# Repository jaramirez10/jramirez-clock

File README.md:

# jramirez-clock
 This repository contains all files pertaining to my PCB clock design and development as part of the Google Hardware Product Sprint.

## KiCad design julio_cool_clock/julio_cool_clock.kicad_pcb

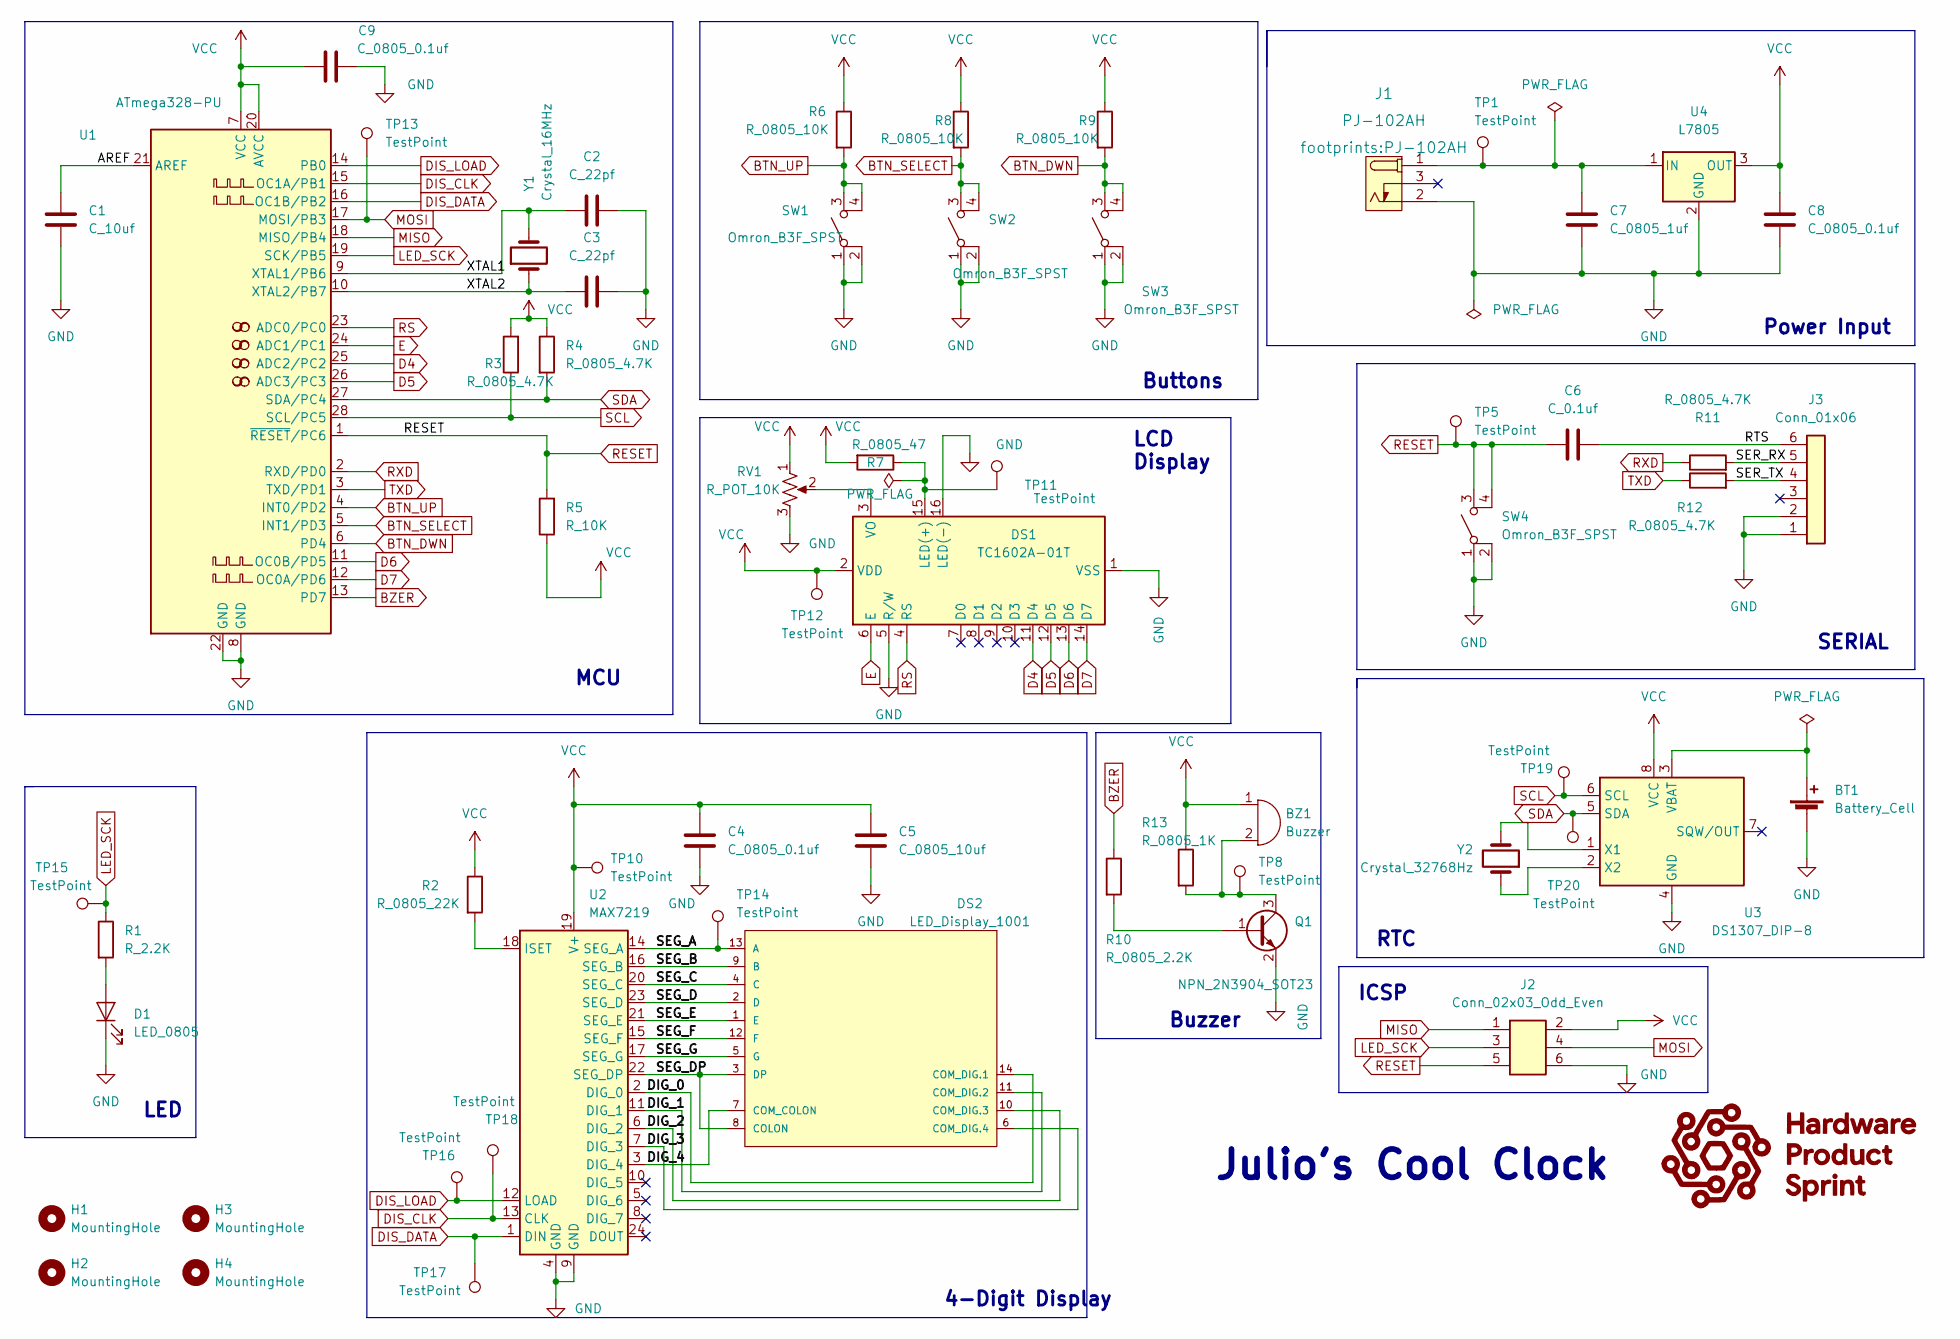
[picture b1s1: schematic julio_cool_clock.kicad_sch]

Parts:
BT1: Battery_Cell; BatteryHolder_Keystone_106_1x20mm; MPN BS-7; Digikey PN BS-7-ND
BZ1: Buzzer; Buzzer_TDK_PS1240P02BT_D12.2mm_H6.5mm; MPN PS1420P02CT; Digikey PN 445-2526-1-ND
C1: C_10uf; C_0805_2012Metric; Voltage N/A; Tolerance N/A; MPN GRM21BR61E106KA73L; Digikey PN 490-5523-1-ND
C2, C3: C_22pf; C_0805_2012Metric; Voltage N/A; Tolerance N/A; MPN CC0805JRNPO9BN220; Digikey PN 311-1103-1-ND
C4, C8, C9: C_0805_0.1uf; C_0805_2012Metric; Voltage N/A; Tolerance N/A; MPN 08055C104KAT2A; Digikey PN 478-1395-1-ND
C5: C_0805_10uf; C_0805_2012Metric; Voltage N/A; Tolerance N/A; MPN GRM21BR61E106KA73L; Digikey PN 490-5523-1-ND
C6: C_0.1uf; C_0805_2012Metric; Voltage N/A; Tolerance N/A; MPN 08055C104KAT2A; Digikey PN 478-1395-1-ND
C7: C_0805_1uf; C_0805_2012Metric; Voltage N/A; Tolerance N/A; MPN CC0805KKX7R8BB105; Digikey PN 311-1456-1-ND
D1: LED_0805; LED_0805_2012Metric; MPN 150080RS75000; Digikey PN 732-4984-1-ND
DS1: TC1602A-01T; MPN 1447; Digikey PN 1528-2212-ND
DS2: LED_Display_1001; Adafruit-1001-0-0-MFG; forward voltage 3.2V; reverse voltage 5V; mouser part number 485-1001; digikey description WHITE 7-SEGMENT CLOCK DISPLAY
H1, H2, H3, H4: MountingHole; MountingHole_3.2mm_M3
J1: PJ-102AH; MPN PJ-102AH; Digikey PN CP-102AH-ND
J2: Conn_02x03_Odd_Even; PinHeader_2x03_P2.54mm_Vertical; MPN PRPC003DAAN-RC; Digikey PN S2011EC-03-ND
J3: Conn_01x06; PinHeader_1x06_P2.54mm_Vertical; MPN 61300611121; Digikey PN 732-5319-ND
Q1: NPN_2N3904_SOT23; SOT-23; MPN CMPT3904E TR PBFREE; Digikey PN 1514-CMPT3904ETRPBFREECT-ND
R1: R_2.2K; R_0805_2012Metric; Tolerance N/A; MPN N/A; Digikey PN 311-2.20KCRCT-ND
R2: R_0805_22K; R_0805_2012Metric; Tolerance N/A; MPN RC0805FR-0722KL; Digikey PN 311-22.0KCRCT-ND
R3, R4, R11, R12: R_0805_4.7K; R_0805_2012Metric; Tolerance N/A; MPN RC0805FR-074K7L; Digikey PN 311-4.70KCRCT-ND
R5: R_10K; R_0805_2012Metric; Tolerance N/A; MPN RC0805FR-0710KL; Digikey PN 311-10.0KCRCT-ND
R6, R8, R9: R_0805_10K; R_0805_2012Metric; Tolerance N/A; MPN RC0805FR-0710KL; Digikey PN 311-10.0KCRCT-ND
R7: R_0805_47; R_0805_2012Metric; Tolerance N/A; Mouser PN N/A; Digikey PN RC0805FR-0747RL
R10: R_0805_2.2K; R_0805_2012Metric; Tolerance N/A; MPN N/A; Digikey PN 311-2.20KCRCT-ND
R13: R_0805_1K; R_0805_2012Metric; Tolerance N/A; Mouser PN N/A; Digikey PN RC0805FR-0710KL
RV1: R_POT_10K; Potentiometer_Bourns_3386P_Vertical; MPN 3386P-1-103TLF; Digikey PN 3386P-103TLF-ND
SW1, SW2, SW3, SW4: Omron_B3F_SPST; SW_SPST_Omron_B3FS-100xP; MPN B3FS-1000P; Digikey PN SW423CT-ND
TP1, TP5, TP8, TP10, TP11, TP12, TP13, TP14, TP15, TP16, TP17, TP18, TP19, TP20: TestPoint; TestPoint_THTPad_D2.0mm_Drill1.0mm
U1: ATmega328-PU; DIP-28_W7.62mm; MPN ED281DT; Digikey PN ED3050-5-ND
U2: MAX7219; DIP-24_W7.62mm; MPN ED241DT; Digikey PN ED3049-5-ND
U3: DS1307_DIP-8; DIP-8_W7.62mm; MPN A 08-LC-TT; Digikey PN AE9986-ND
U4: L7805; TO-252-2; MPN L7805CDT-TR; Digikey PN 497-7255-1-ND
Y1: Crystal_16MHz; Crystal_SMD_HC49-SD; MPN ECS-160-20-5PXDN-TR; Digikey PN XC1299CT-ND
Y2: Crystal_32768Hz; Crystal_SMD_2Pin_3.2x1.5mm; MPN Q 0,032768-JTX310-12,5-20-T1-HMR-50K-LF; Digikey PN 1908-1314-1-ND

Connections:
/AREF: C1.1, U1.21 (AREF)
/DIG_0: DS2.14 (COM_DIG.1), U2.2 (DIG_0)
/DIG_1: DS2.11 (COM_DIG.2), U2.11 (DIG_1)
/DIG_2: DS2.10 (COM_DIG.3), U2.6 (DIG_2)
/DIG_3: DS2.6 (COM_DIG.4), U2.7 (DIG_3)
/DIG_4: DS2.7 (COM_COLON), U2.3 (DIG_4)
/RTS: C6.2, J3.6
/SEG_A: DS2.13 (A), TP14.1, U2.14 (SEG_A)
/SEG_B: DS2.9 (B), U2.16 (SEG_B)
/SEG_C: DS2.4 (C), U2.20 (SEG_C)
/SEG_D: DS2.2 (D), U2.23 (SEG_D)
/SEG_DP: DS2.3 (DP), DS2.8 (COLON), U2.22 (SEG_DP)
/SEG_E: DS2.1 (E), U2.21 (SEG_E)
/SEG_F: DS2.12 (F), U2.15 (SEG_F)
/SEG_G: DS2.5 (G), U2.17 (SEG_G)
/SER_RX: J3.5, R11.2
/SER_TX: J3.4, R12.2
/XTAL1: C2.1, U1.9 (XTAL1/PB6), Y1.2
/XTAL2: C3.2, U1.10 (XTAL2/PB7), Y1.1
BTN_DWN: R9.2, SW3.3 (B), SW3.4 (B), U1.6 (PD4)
BTN_SELECT: R8.2, SW2.3 (B), SW2.4 (B), U1.5 (INT1/PD3)
BTN_UP: R6.2, SW1.3 (B), SW1.4 (B), U1.4 (INT0/PD2)
BZER: R10.1, U1.13 (PD7)
D4: DS1.11 (D4), U1.25 (ADC2/PC2)
D5: DS1.12 (D5), U1.26 (ADC3/PC3)
D6: DS1.13 (D6), U1.11 (OC0B/PD5)
D7: DS1.14 (D7), U1.12 (OC0A/PD6)
DIS_CLK: TP18.1, U1.15 (OC1A/PB1), U2.13 (CLK)
DIS_DATA: TP17.1, U1.16 (OC1B/PB2), U2.1 (DIN)
DIS_LOAD: TP16.1, U1.14 (PB0), U2.12 (LOAD)
E: DS1.6 (E), U1.24 (ADC1/PC1)
GND: BT1.2 (-), C1.2, C2.2, C3.1, C4.2, C5.2, C7.2, C8.2, C9.2, D1.1 (K), DS1.1 (VSS), DS1.5 (R/W), DS1.16 (LED(-)), J1.2 (OUT), J2.6, J3.1, J3.2, Q1.2 (E), RV1.3, SW1.1 (A), SW1.2 (A), SW2.1 (A), SW2.2 (A), SW3.1 (A), SW3.2 (A), SW4.1 (A), SW4.2 (A), U1.8 (GND), U1.22 (GND), U2.4 (GND), U2.9 (GND), U3.4 (GND), U4.2 (GND)
LED_SCK: J2.3, R1.1, TP15.1, U1.19 (SCK/PB5)
MISO: J2.1, U1.18 (MISO/PB4)
MOSI: J2.4, TP13.1, U1.17 (MOSI/PB3)
unnamed: BT1.1 (+), U3.3 (VBAT)
unnamed: BZ1.2 (+), Q1.3 (C), R13.2, TP8.1
unnamed: C7.1, J1.1 (POLE), TP1.1, U4.1 (IN)
unnamed: D1.2 (A), R1.2
unnamed: DS1.3 (VO), RV1.2
unnamed: DS1.15 (LED(+)), R7.1, TP11.1
unnamed: Q1.1 (B), R10.2
unnamed: R2.2, U2.18 (ISET)
unnamed: U3.1 (X1), Y2.2
unnamed: U3.2 (X2), Y2.1
RESET: C6.1, J2.5, R5.2, SW4.3 (B), SW4.4 (B), TP5.1, U1.1 (~RESET/PC6)
RS: DS1.4 (RS), U1.23 (ADC0/PC0)
RXD: R11.1, U1.2 (RXD/PD0)
SCL: R3.1, TP19.1, U1.28 (SCL/PC5), U3.6 (SCL)
SDA: R4.2, TP20.1, U1.27 (SDA/PC4), U3.5 (SDA)
TXD: R12.1, U1.3 (TXD/PD1)
VCC: BZ1.1 (-), C4.1, C5.1, C8.1, C9.1, DS1.2 (VDD), J2.2, R2.1, R3.2, R4.1, R5.1, R6.1, R7.2, R8.1, R9.1, R13.1, RV1.1, TP10.1, TP12.1, U1.7 (VCC), U1.20 (AVCC), U2.19 (V+), U3.8 (VCC), U4.3 (OUT)

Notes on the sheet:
Buttons
MCU
Power Input
LCD Display
LED
Julio's Cool Clock
RTC
4-Digit Display
SERIAL
Buzzer
ICSP

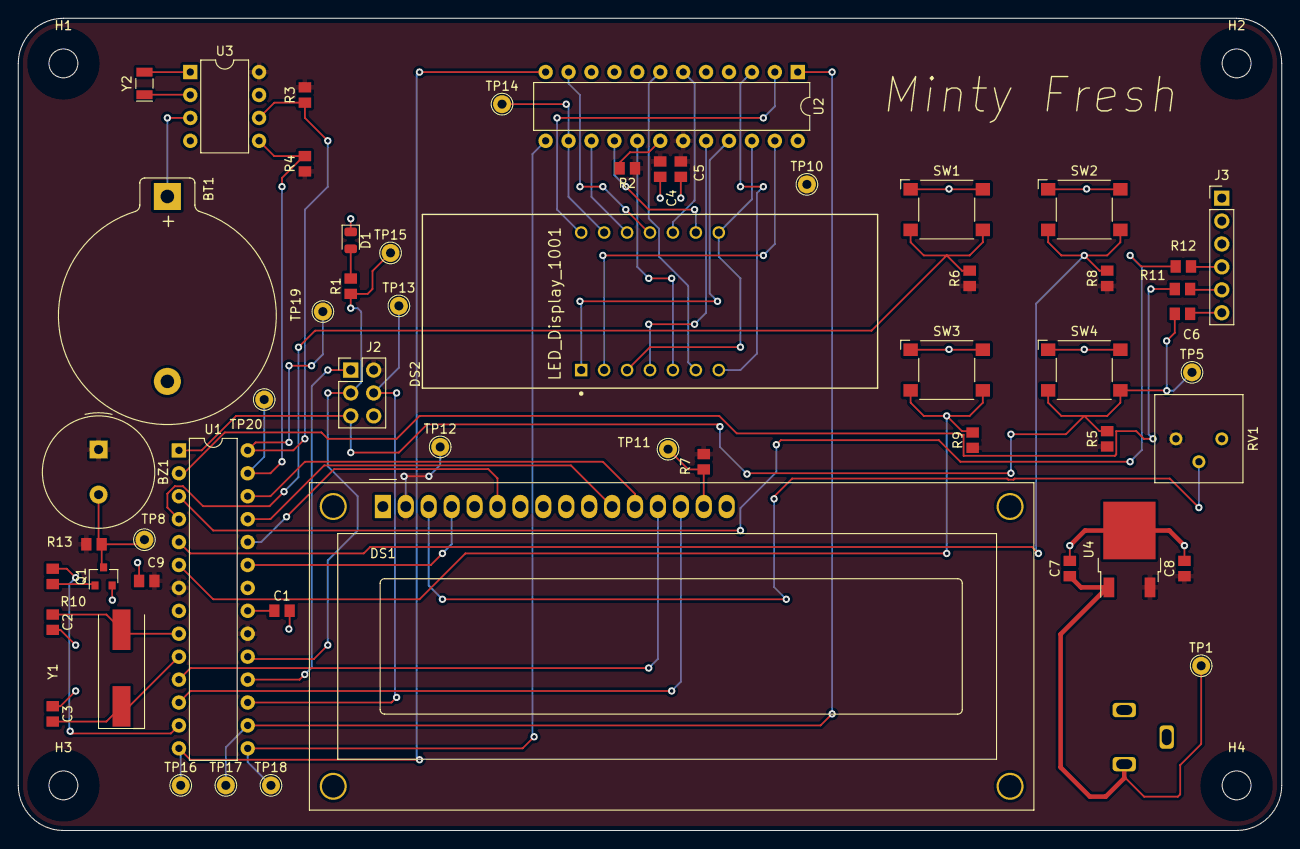
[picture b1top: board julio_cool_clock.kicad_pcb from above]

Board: 2 copper layers, 140.0 x 90.0 mm, 60 parts (1 on the bottom side), 52 nets.

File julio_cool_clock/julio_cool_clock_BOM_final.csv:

"Id";"Designator";"Package";"Quantity";"Designation";"Supplier and ref";
1;"R12,R11,R4,R3";"R_0805_2012Metric";4;"R_0805_4.7K";;;
2;"H4,H2,H3,H1";"MountingHole_3.2mm_M3";4;"MountingHole";;;
3;"TP11,TP15,TP12,TP1,TP17,TP19,TP16,TP13,TP5,TP10,TP18,TP8,TP14,TP20";"TestPoint_THTPad_D2.0mm_Drill1.0mm";14;"TestPoint";;;
4;"C5";"C_0805_2012Metric";1;"C_0805_10uf";;;
5;"C8,C4,C9";"C_0805_2012Metric";3;"C_0805_0.1uf";;;
6;"DS1";"TC1602A-01T";1;"TC1602A-01T";;;
7;"R7";"R_0805_2012Metric";1;"R_0805_47";;;
8;"BZ1";"Buzzer_TDK_PS1240P02BT_D12.2mm_H6.5mm";1;"Buzzer";;;
9;"R13";"R_0805_2012Metric";1;"R_0805_1K";;;
10;"C6";"C_0805_2012Metric";1;"C_0.1uf";;;
11;"R10";"R_0805_2012Metric";1;"R_0805_2.2K";;;
12;"SW2,SW4,SW3,SW1";"SW_SPST_Omron_B3FS-100xP";4;"Omron_B3F_SPST";;;
13;"Y1";"Crystal_SMD_HC49-SD";1;"Crystal_16MHz";;;
14;"R2";"R_0805_2012Metric";1;"R_0805_22K";;;
15;"U1";"DIP-28_W7.62mm";1;"ATmega328-PU";;;
16;"C3,C2";"C_0805_2012Metric";2;"C_22pf";;;
17;"RV1";"Potentiometer_Bourns_3386P_Vertical";1;"R_POT_10K";;;
18;"C1";"C_0805_2012Metric";1;"C_10uf";;;
19;"J2";"PinHeader_2x03_P2.54mm_Vertical";1;"Conn_02x03_Odd_Even";;;
20;"Q1";"SOT-23";1;"NPN_2N3904_SOT23";;;
21;"R6,R9,R8";"R_0805_2012Metric";3;"R_0805_10K";;;
22;"J3";"PinHeader_1x06_P2.54mm_Vertical";1;"Conn_01x06";;;
23;"U2";"DIP-24_W7.62mm";1;"MAX7219";;;
24;"Y2";"Crystal_SMD_2Pin_3.2x1.5mm";1;"Crystal_32768Hz";;;
25;"R1";"R_0805_2012Metric";1;"R_2.2K";;;
26;"D1";"LED_0805_2012Metric";1;"LED_0805";;;
27;"U3";"DIP-8_W7.62mm";1;"DS1307_DIP-8";;;
28;"DS2";"Adafruit-1001-0-0-MFG";1;"LED_Display_1001";;;
29;"U4";"TO-252-2";1;"L7805";;;
30;"BT1";"BatteryHolder_Keystone_106_1x20mm";1;"Battery_Cell";;;
31;"C7";"C_0805_2012Metric";1;"C_0805_1uf";;;
32;"R5";"R_0805_2012Metric";1;"R_10K";;;
33;"J1";"PJ-102AH";1;"VAL**";;;

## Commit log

2022-06-02 Design Commit 1
2022-06-10 Clock Design 1
2022-06-11 New Blinking Speed Commit
    Here is the firmware with the new LED blinking speed as part of the Week 1 deliverables.
2022-06-12 Design Commit 1.1
    Adjusted the starting schematic with 10uF capacitors in place of the polar capacitors in the lecture slide.
2022-06-17 Design Commit 2
    In this commit, I adjusted the MCU schematic section and added the power input portion.
2022-06-20 Design Commit 2.1
    Converted the RESET, RXD, and TXD labels from global inputs to outputs
2022-06-27 Design Commit 3
    Cleaned up the existing components and added inputs + outputs to the schematic as well.
2022-07-04 Design Commit 4
    I refined the schematic and added the RTC, buttons, and the LCD display for my clock.
2022-07-04 Design Commit 4.1
    Fixed some wiring that was undone.
2022-07-06 Design Commit 4.2
    Arranged components from schematic onto PCB.
2022-07-11 Design Commit 5
    Pushed Netlist to PCB and made initial placement of all components, including UI components.
2022-07-17 Design Commit 6
    Added prelim DFT features, completed PCB routing, and shipped first Gerber out.
2022-07-21 Final Gerber
    Git commit for final Gerber Out. I forgot to upload the Google Form for the initial Gerber but everything from the first one is in the previous Git commit.
2022-07-21 Gerber Out Revisions 1
2022-07-21 Final Gerber Out (with revisions)
2022-08-01 MTP Firmware Commit
    First commit for MTP. Program includes code for all components used in my clock.
2022-08-08 MTP Firmware Commit 2
    Made revisions to programs to test the buzzer and buttons after rewiring my dev board. This commit includes all individual MTPs for each I/O as well as one compiled MTP that is used for the entire cl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
2023-08-17 Update README.md 8/17
2023-09-10 Update README.md
    Revised README language.
2024-01-26 Update README.md
    Changed language to README
